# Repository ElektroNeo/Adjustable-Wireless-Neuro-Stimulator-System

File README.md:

# Adjustable Wireless Neuro Stimulator System
This project is made for the Design Project lecture. With this system, you can control output current by using Android application which made with [App Inventor](http://ai2.appinventor.mit.edu/).
### Notes
- The maximum output current is 5.5mA.
- The maximum Pulse High, Pulse Low, and Working Time values on the application are 255.
- Current source and system power supplies must not share the same ground.

## Used Microcontroller Features
In the software used PIC16F1713 microcontroller features listed below.
- DAC
- EUSART
- Timer0
- Interrupt

## Components
- 1x PIC16F1713 Microcontroller
- 1x HC-06 Bluethoot Module
- 2x LMC6482IN Amplifier
- 1x L7805 5V Regulator
- 3x Screw Terminal
- +12V DC Power Supply (for the current source)
- +7V - +12V DC Power Supply or Battery (for the system)
- 2x 120 Ohm Resistor
- 2x 560 Ohm Resistor
- 3x 1k Ohm Resistor
- 2x 330 Ohm Resistor
- 2x 10uF Capacitor
- 2x Red LED
- 1x Green LED
- Others (Button, pin header, switch)

## App
| Disconnected App  | Connected App |
| :-------------: | :-------------: |
|   |   |

## Schematic
|   |  |
| :-------------: | :-------------: |
|   |   |
|   |   |
|   |   |

## 3D Design

## Product

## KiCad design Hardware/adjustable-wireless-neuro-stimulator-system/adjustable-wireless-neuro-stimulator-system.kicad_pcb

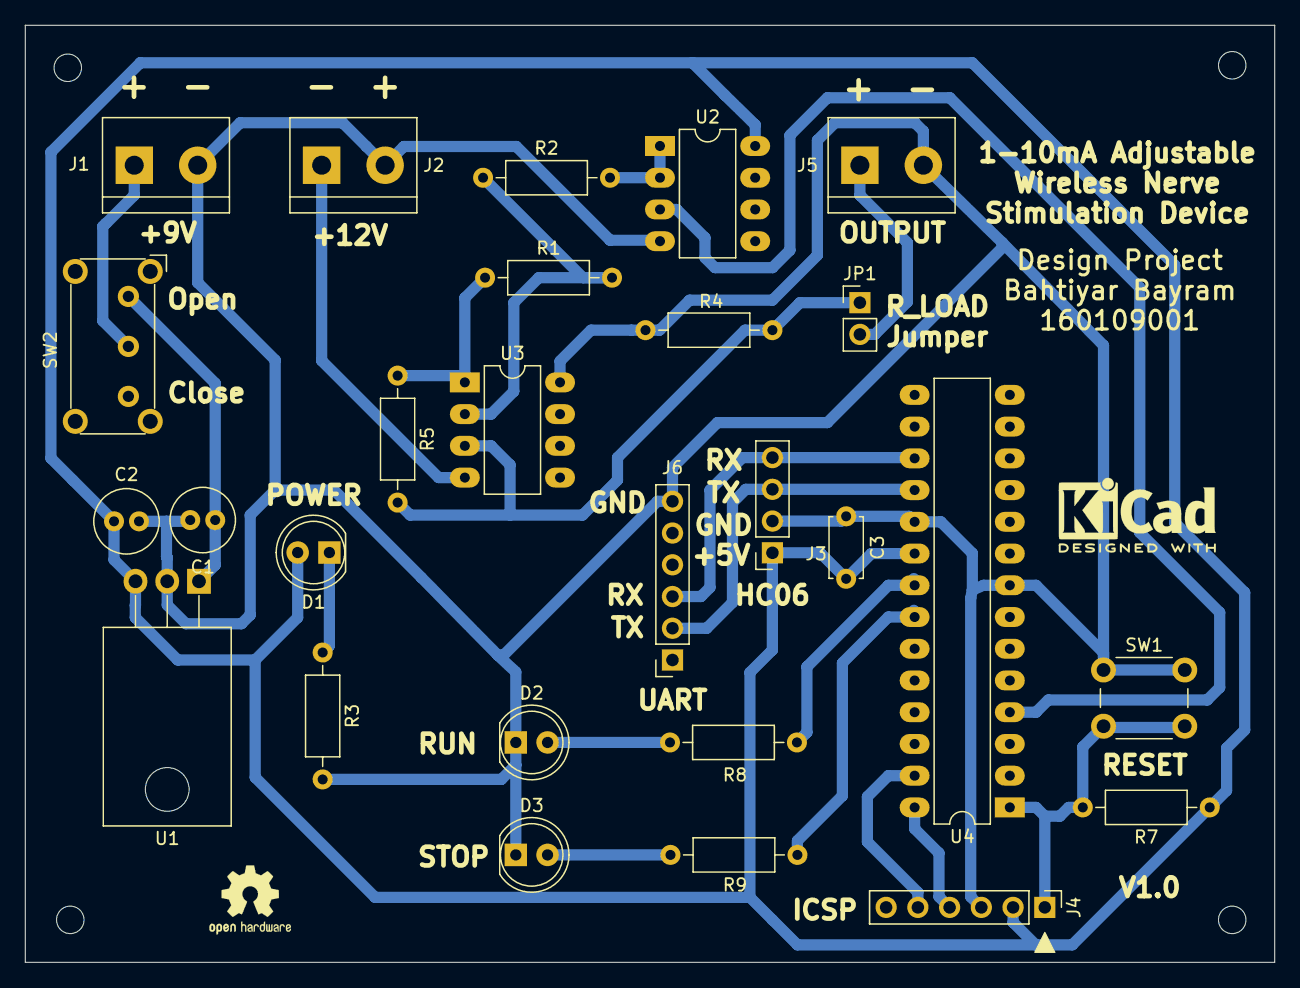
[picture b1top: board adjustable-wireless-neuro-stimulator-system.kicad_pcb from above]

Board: 2 copper layers, 100.0 x 75.0 mm, 27 parts (0 on the bottom side), 21 nets.

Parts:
C1: 0.33uF; C_Radial_D5.0mm_H11.0mm_P2.00mm
C2: 0.1uF; C_Radial_D5.0mm_H11.0mm_P2.00mm
C3: 100nF; C_Disc_D4.7mm_W2.5mm_P5.00mm
D1: PWR; LED_D5.0mm
D2: RUN; LED_D5.0mm
D3: STOP; LED_D5.0mm
J1: PWR IN; TerminalBlock_bornier-2_P5.08mm
J2: 12V PWR IN; TerminalBlock_bornier-2_P5.08mm
J3: HC06; PinSocket_1x04_P2.54mm_Vertical
J4: ICSP; PinHeader_1x06_P2.54mm_Vertical
J5: Output Probe; TerminalBlock_bornier-2_P5.08mm
J6: UART_Debug; PinSocket_1x06_P2.54mm_Vertical
JP1: R_LOAD; PinHeader_1x02_P2.54mm_Vertical
R1, R5: 120; R_Axial_DIN0207_L6.3mm_D2.5mm_P10.16mm_Horizontal
R2, R4: 560; R_Axial_DIN0207_L6.3mm_D2.5mm_P10.16mm_Horizontal
R3: 1k; R_Axial_DIN0207_L6.3mm_D2.5mm_P10.16mm_Horizontal
R7: 10k; R_Axial_DIN0207_L6.3mm_D2.5mm_P10.16mm_Horizontal
R8, R9: 470; R_Axial_DIN0207_L6.3mm_D2.5mm_P10.16mm_Horizontal
SW1: RESET; SW_PUSH_6mm_H5mm
SW2: Power SW; SW_E-Switch_EG1224_SPDT_Angled
U1: L7805; TO-220-3_Horizontal_TabDown
U2, U3: LMC6482; DIP-8_W7.62mm_LongPads
U4: PIC16F1713-ISP; DIP-28_W7.62mm_LongPads

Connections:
+5V: C2.1, C3.2, D1.2, J3.1, J4.2, R7.1, U1.3, U2.8, U4.20
-12V: J2.1, U3.4
/DAC1OUT1: U2.3, U4.4
/ICSPCLK: J4.5, U4.27
/ICSPDAT: J4.4, U4.28
/RX: J3.4, J6.3, U4.17
/RX_MCU: J3.3, J6.2, U4.18
/~MCLR: J4.1, R7.2, SW1.2, U4.1
GND: C1.2, C2.2, C3.1, D2.1, D3.1, J1.2, J2.2, J3.2, J4.3, J5.2, J6.6, R3.2, R4.2, SW1.1, U1.2, U2.4, U3.8, U4.8, U4.19
unnamed: C1.1, SW2.1, U1.1
unnamed: D1.1, R3.1
unnamed: D2.2, R8.1
unnamed: D3.2, R9.1
unnamed: J5.1, JP1.2
unnamed: JP1.1, R4.1, R5.2, U3.3
unnamed: R1.1, R5.1, U3.1
unnamed: R1.2, R2.1, U3.2
unnamed: R2.2, U2.1, U2.2
unnamed: R8.2, U4.21
unnamed: R9.2, U4.22
VCC: J1.1, SW2.2

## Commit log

2020-06-10 Initial commit.
    - Hardware v1.0
    - Software v1.0
    - App v2.0
2020-06-11 Renaming.
